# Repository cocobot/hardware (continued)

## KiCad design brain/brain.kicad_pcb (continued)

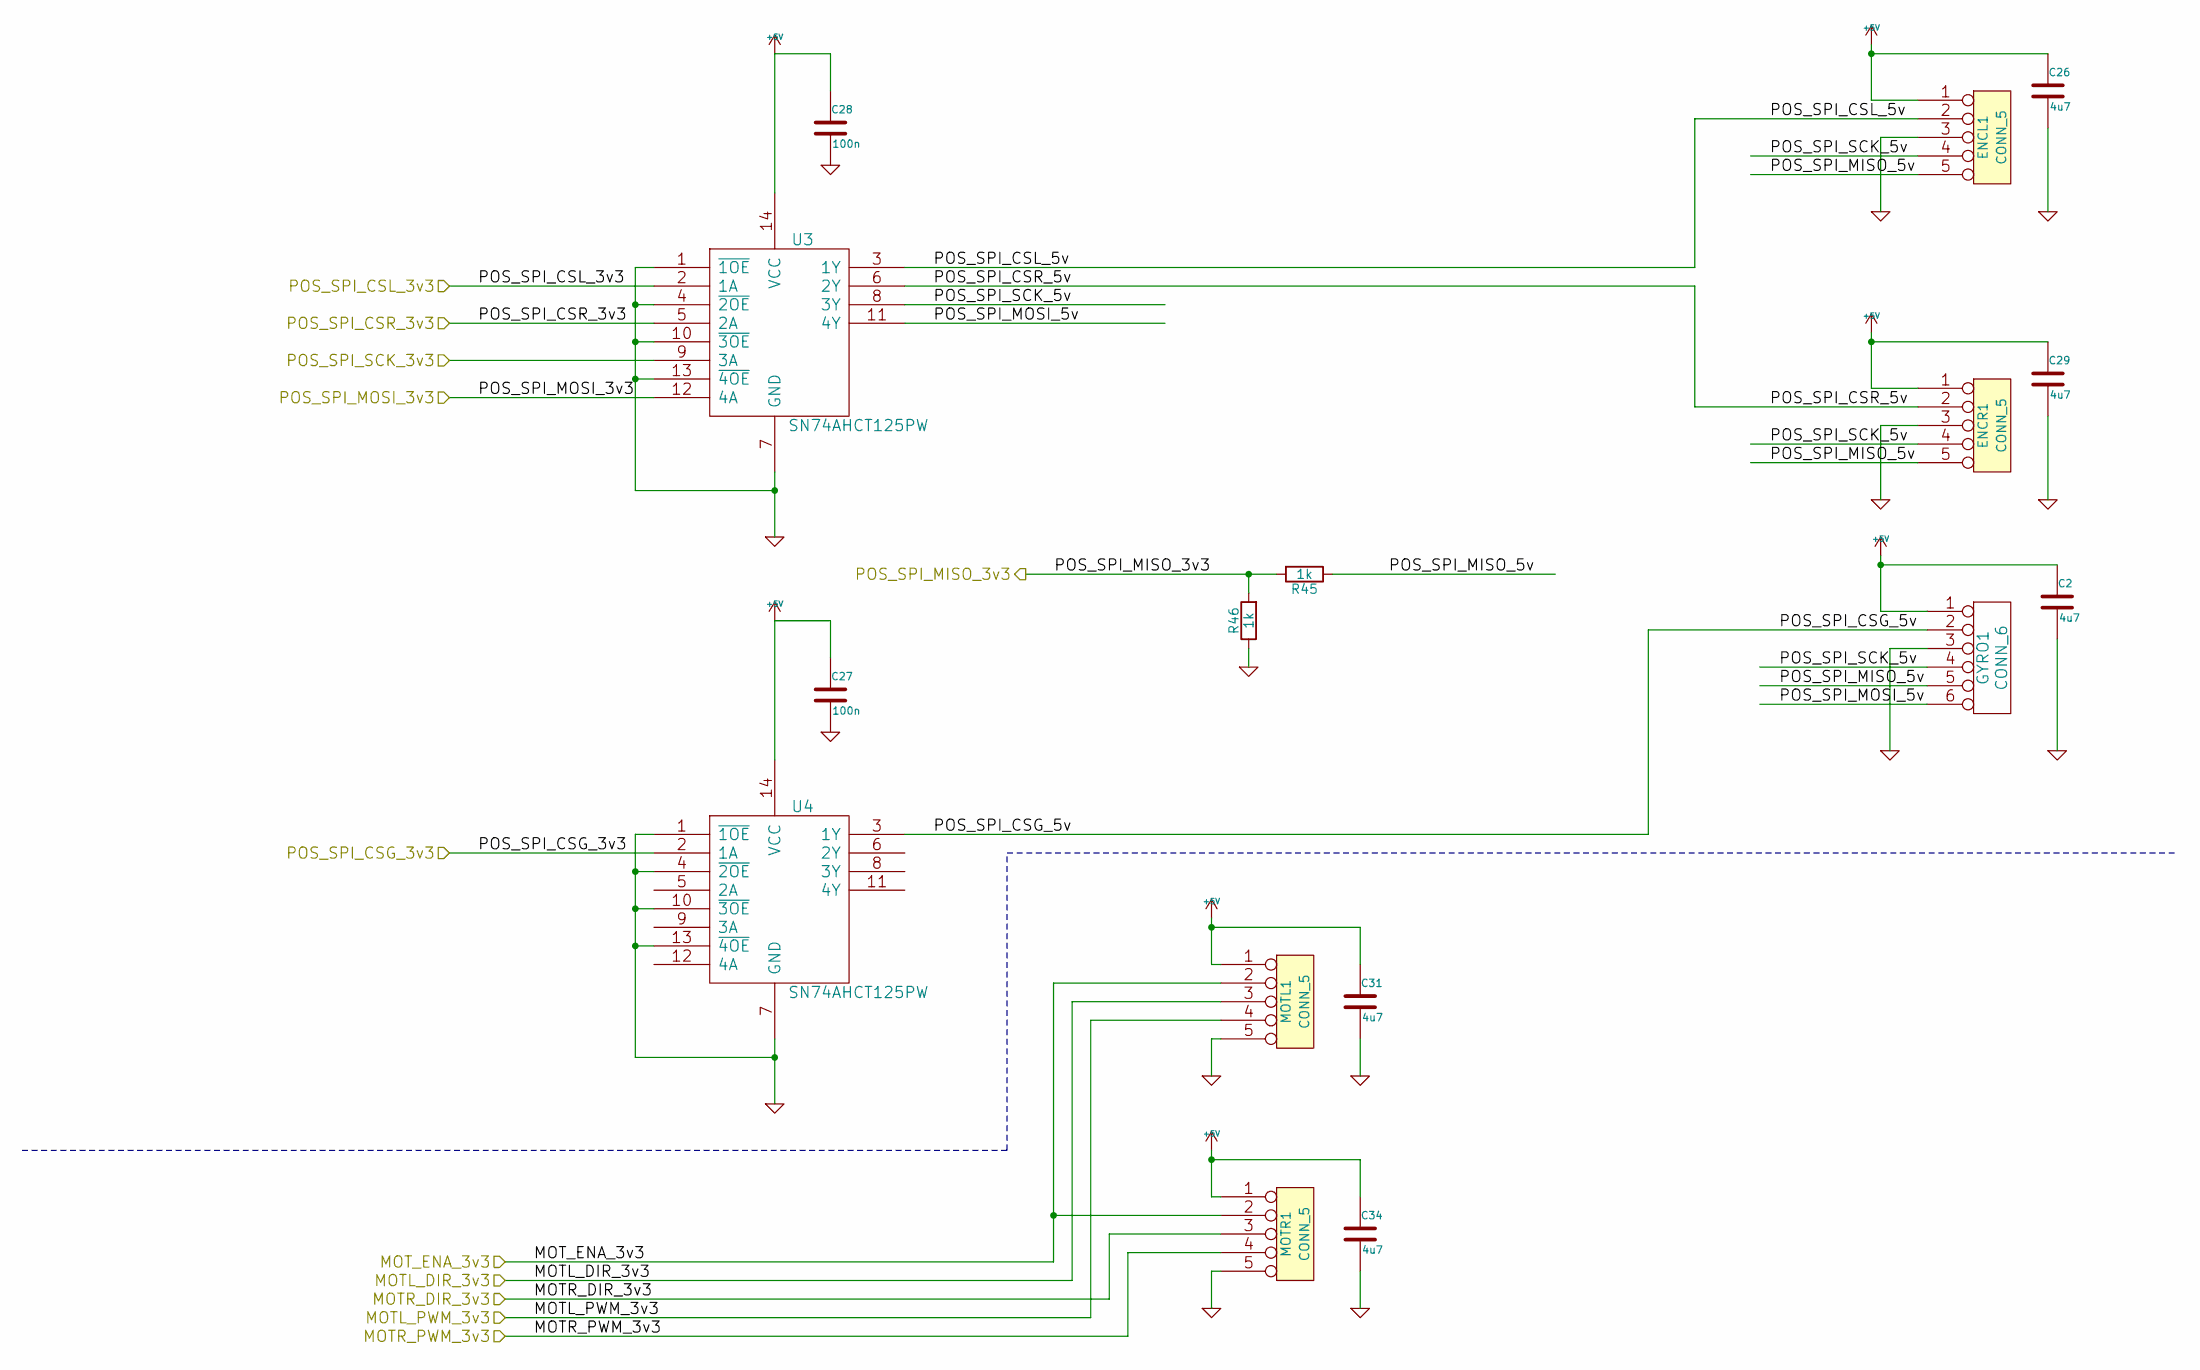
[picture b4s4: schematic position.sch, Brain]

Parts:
C2, C26, C29, C31, C34: 4u7; C_0603
C27, C28: 100n; C_0603
ENCL1: CONN_5; Socket_MOLEX-KK-RM2-54mm_Lock_5pin_straight
ENCR1: CONN_5; Socket_MOLEX-KK-RM2-54mm_Lock_5pin_straight
GYRO1: CONN_6; Socket_MOLEX-KK-RM2-54mm_Lock_6pin_straight
MOTL1: CONN_5; Socket_MOLEX-KK-RM2-54mm_Lock_5pin_straight
MOTR1: CONN_5; Socket_MOLEX-KK-RM2-54mm_Lock_5pin_straight
R45, R46: 1k; R_0603
U3, U4: SN74AHCT125PW; TSSOP-14_4.4x5mm_Pitch0.65mm

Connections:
+5V: C2.1, C26.1, C27.1, C28.1, C29.1, C31.1, C34.1, ENCL1.1, ENCR1.1, GYRO1.1, MOTL1.1, MOTR1.1, U3.14 (VCC), U4.14 (VCC); also elsewhere on the board
/DC motor/MOT_ENA_3v3: MOTL1.2, MOTR1.2; also elsewhere on the board
/Position/MOTL_DIR_3v3: MOTL1.3; also elsewhere on the board
/Position/MOTL_PWM_3v3: MOTL1.4; also elsewhere on the board
/Position/MOTR_DIR_3v3: MOTR1.3; also elsewhere on the board
/Position/MOTR_PWM_3v3: MOTR1.4; also elsewhere on the board
/Position/POS_SPI_CSG_3v3: U4.2 (1A); also elsewhere on the board
/Position/POS_SPI_CSG_5v: GYRO1.2, U4.3 (1Y)
/Position/POS_SPI_CSL_3v3: U3.2 (1A); also elsewhere on the board
/Position/POS_SPI_CSL_5v: ENCL1.2, U3.3 (1Y)
/Position/POS_SPI_CSR_3v3: U3.5 (2A); also elsewhere on the board
/Position/POS_SPI_CSR_5v: ENCR1.2, U3.6 (2Y)
/Position/POS_SPI_MISO_3v3: R45.2, R46.2; also elsewhere on the board
/Position/POS_SPI_MISO_5v: ENCL1.5, ENCR1.5, GYRO1.5, R45.1
/Position/POS_SPI_MOSI_3v3: U3.12 (4A); also elsewhere on the board
/Position/POS_SPI_MOSI_5v: GYRO1.6, U3.11 (4Y)
/Position/POS_SPI_SCK_3v3: U3.9 (3A); also elsewhere on the board
/Position/POS_SPI_SCK_5v: ENCL1.4, ENCR1.4, GYRO1.4, U3.8 (3Y)
GND: C2.2, C26.2, C27.2, C28.2, C29.2, C31.2, C34.2, ENCL1.3, ENCR1.3, GYRO1.3, MOTL1.5, MOTR1.5, R46.1, U3.1 (~1OE), U3.4 (~2OE), U3.7 (GND), U3.10 (~3OE), U3.13 (~4OE), U4.1 (~1OE), U4.4 (~2OE), U4.7 (GND), U4.10 (~3OE), U4.13 (~4OE); also elsewhere on the board

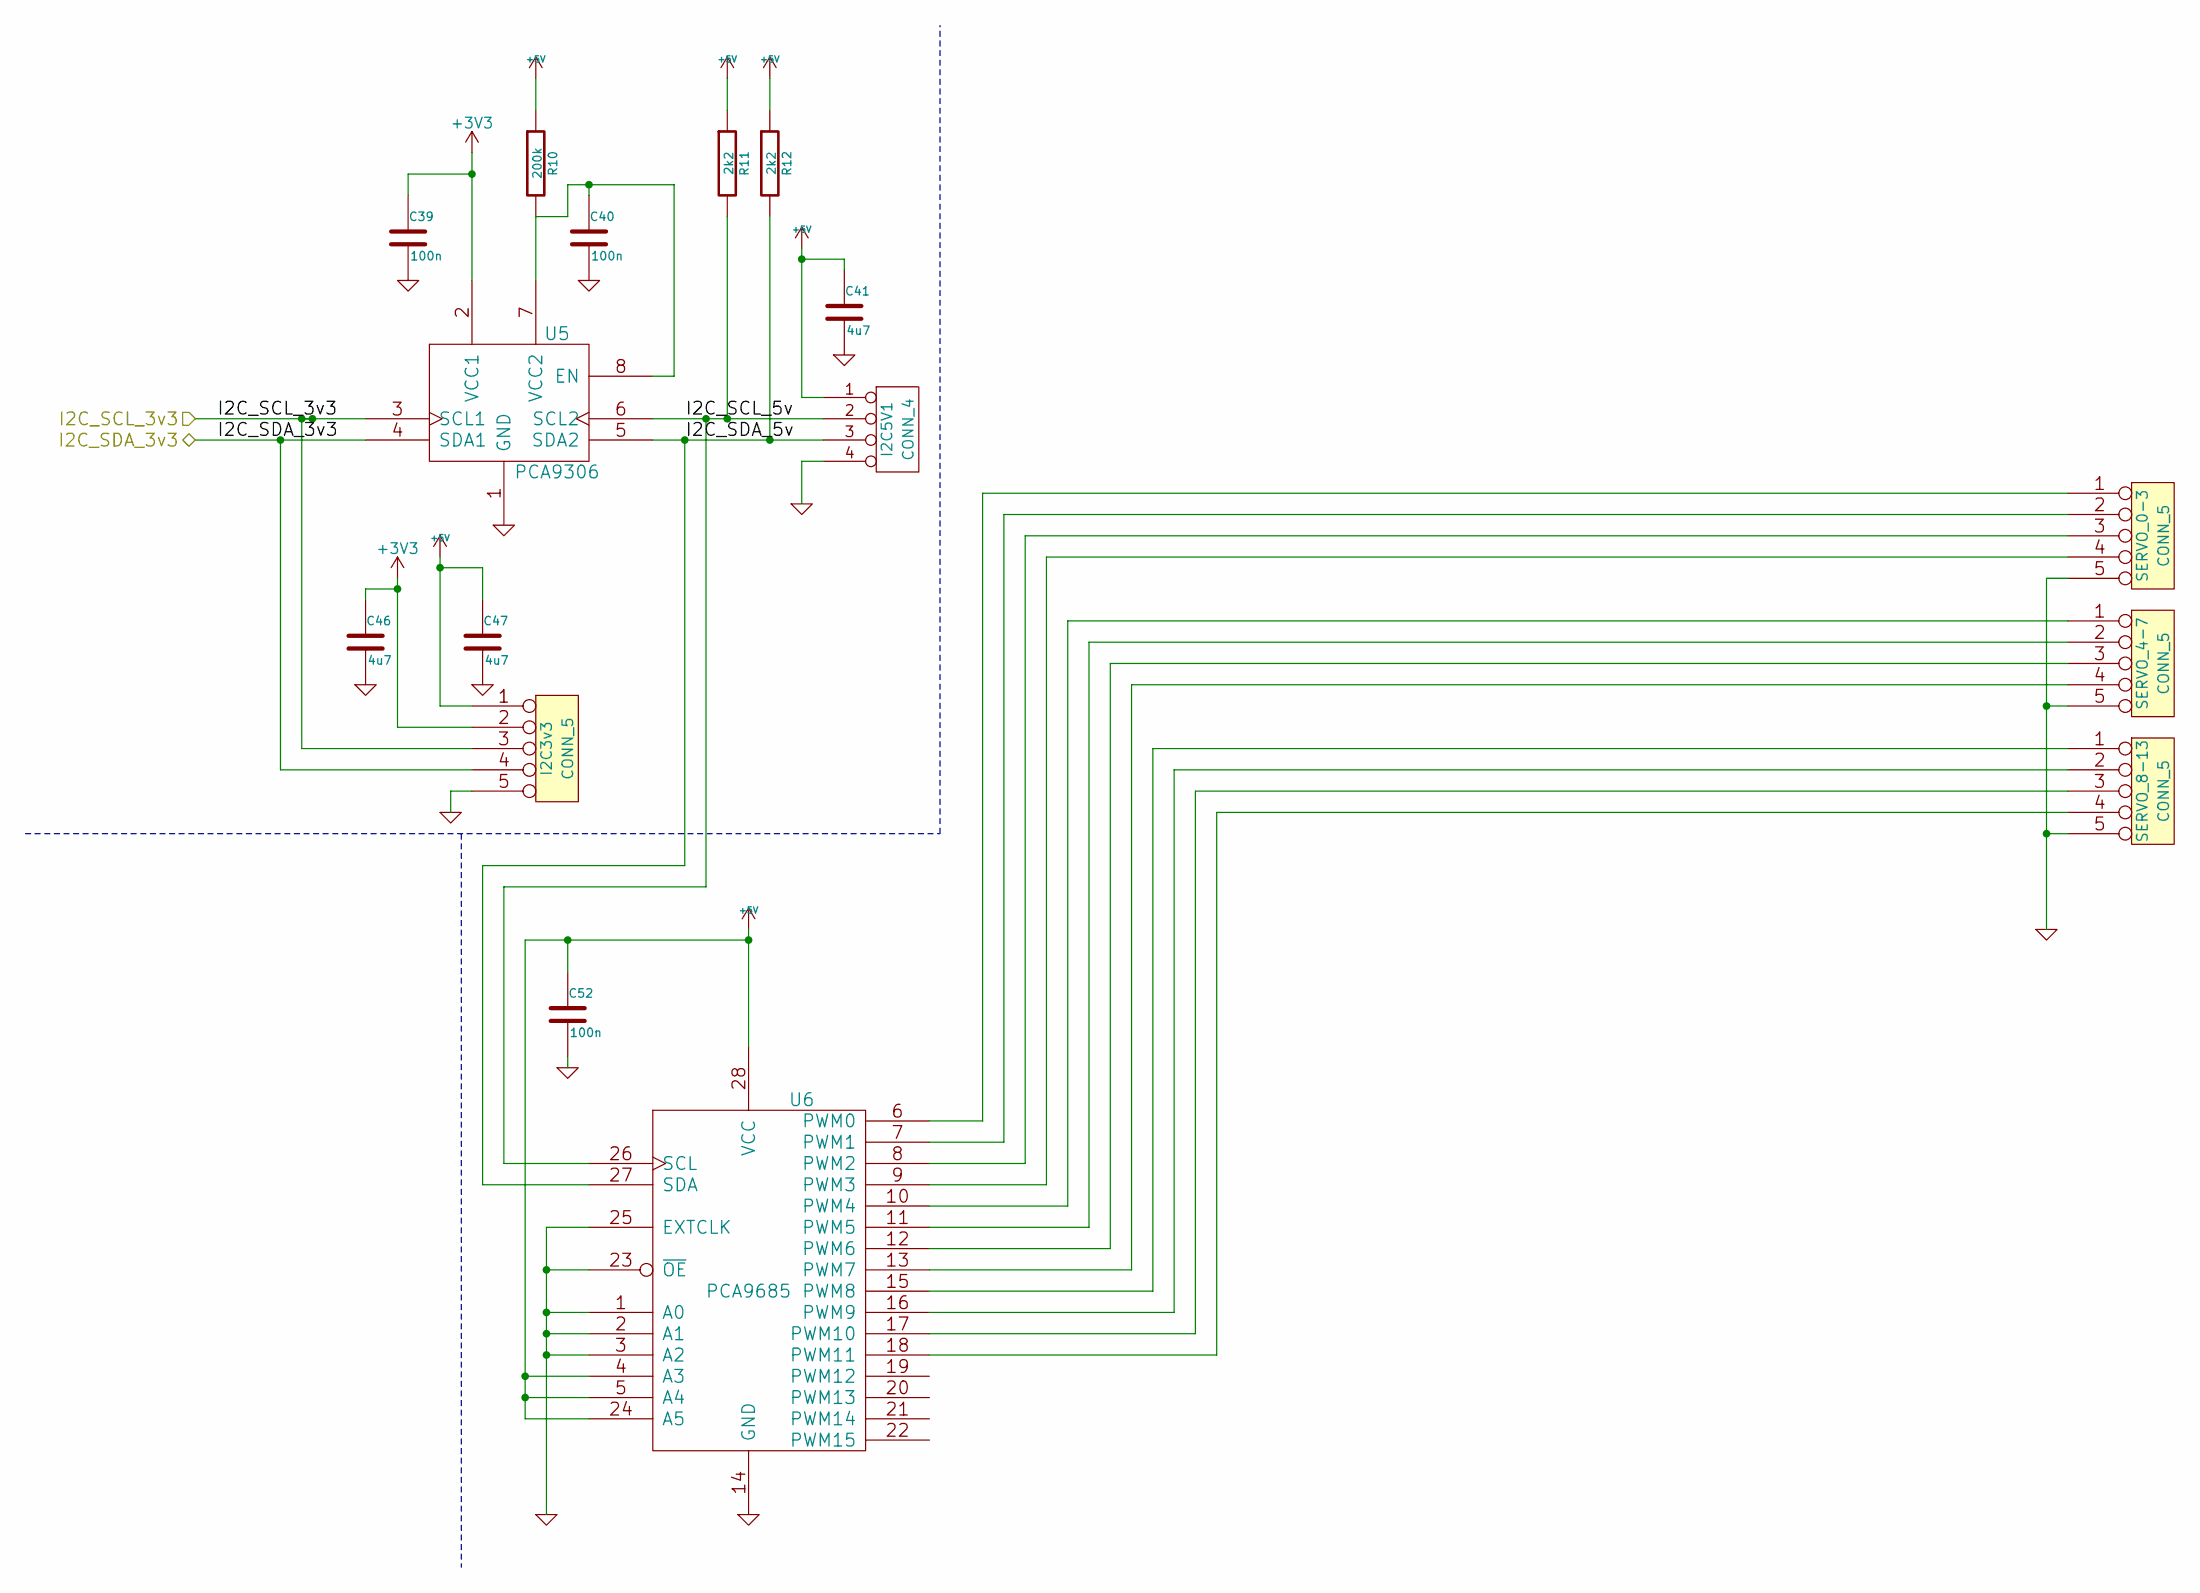
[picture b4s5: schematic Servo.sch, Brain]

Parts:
C39, C40, C52: 100n; C_0603
C41, C46, C47: 4u7; C_0603
I2C3v3: CONN_5; Socket_MOLEX-KK-RM2-54mm_Lock_5pin_straight
I2C5V1: CONN_4; Socket_MOLEX-KK-RM2-54mm_Lock_4pin_straight
R10: 200k; R_0603
R11, R12: 2k2; R_0603
SERVO_0-3, SERVO_4-7, SERVO_8-13: CONN_5; Socket_MOLEX-KK-RM2-54mm_Lock_5pin_straight
U5: PCA9306; SO-8
U6: PCA9685; TSSOP-28_4.4x9.7mm_Pitch0.65mm

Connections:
+3V3: C39.1, C46.1, I2C3v3.2, U5.2 (VCC1); also elsewhere on the board
+5V: C41.1, C47.1, C52.1, I2C3v3.1, I2C5V1.1, R10.1, R11.1, R12.1, U6.4 (A3), U6.5 (A4), U6.24 (A5), U6.28 (VCC); also elsewhere on the board
/Servo/I2C_SCL_3v3: I2C3v3.3, U5.3 (SCL1); also elsewhere on the board
/Servo/I2C_SCL_5v: I2C5V1.2, R11.2, U5.6 (SCL2), U6.26 (SCL)
/Servo/I2C_SDA_3v3: I2C3v3.4, U5.4 (SDA1); also elsewhere on the board
/Servo/I2C_SDA_5v: I2C5V1.3, R12.2, U5.5 (SDA2), U6.27 (SDA)
GND: C39.2, C40.2, C41.2, C46.2, C47.2, C52.2, I2C3v3.5, I2C5V1.4, SERVO_0-3.5, SERVO_4-7.5, SERVO_8-13.5, U5.1 (GND), U6.1 (A0), U6.2 (A1), U6.3 (A2), U6.14 (GND), U6.23 (~OE), U6.25 (EXTCLK); also elsewhere on the board
unnamed: C40.1, R10.2, U5.7 (VCC2), U5.8 (EN)
unnamed: SERVO_0-3.1, U6.6 (PWM0)
unnamed: SERVO_0-3.2, U6.7 (PWM1)
unnamed: SERVO_0-3.3, U6.8 (PWM2)
unnamed: SERVO_0-3.4, U6.9 (PWM3)
unnamed: SERVO_4-7.1, U6.10 (PWM4)
unnamed: SERVO_4-7.2, U6.11 (PWM5)
unnamed: SERVO_4-7.3, U6.12 (PWM6)
unnamed: SERVO_4-7.4, U6.13 (PWM7)
unnamed: SERVO_8-13.1, U6.15 (PWM8)
unnamed: SERVO_8-13.2, U6.16 (PWM9)
unnamed: SERVO_8-13.3, U6.17 (PWM10)
unnamed: SERVO_8-13.4, U6.18 (PWM11)

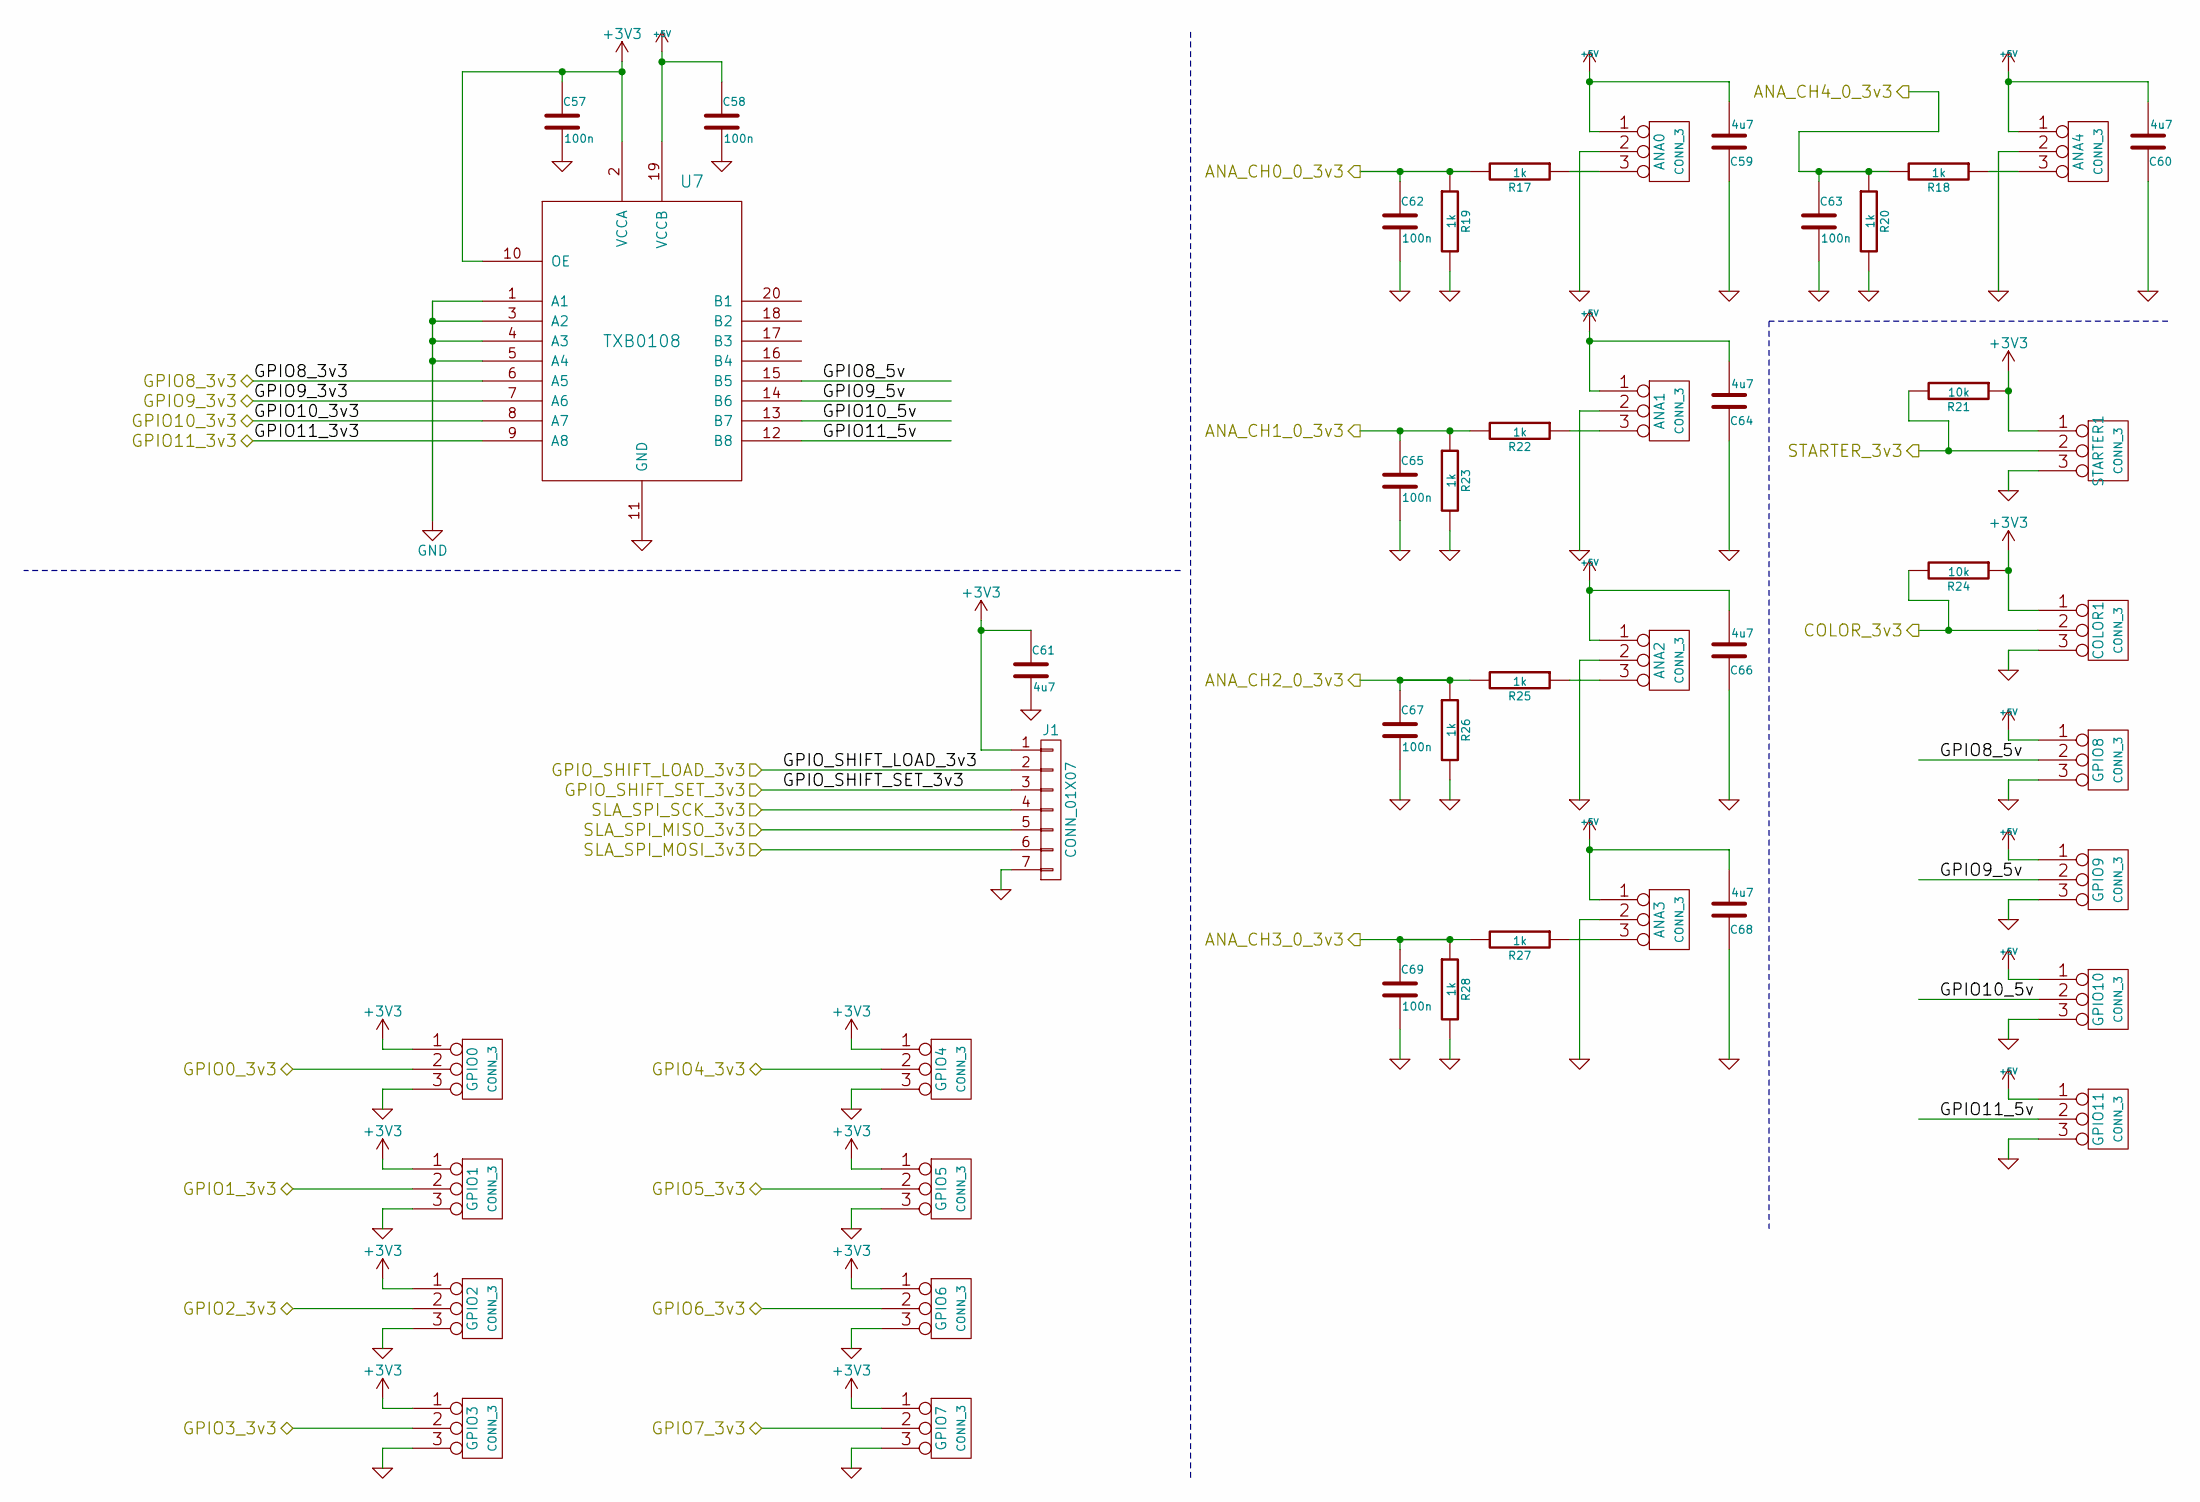
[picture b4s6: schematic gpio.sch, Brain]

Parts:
ANA0, ANA1, ANA2, ANA3, ANA4: CONN_3; Socket_MOLEX-KK-RM2-54mm_Lock_3pin_straight
C57, C58, C62, C63, C65, C67, C69: 100n; C_0603
C59, C60, C61, C64, C66, C68: 4u7; C_0603
COLOR1: CONN_3; Socket_MOLEX-KK-RM2-54mm_Lock_3pin_straight
GPIO0, GPIO1, GPIO2, GPIO3, GPIO4, GPIO5, GPIO6, GPIO7, GPIO8, GPIO9, GPIO10, GPIO11: CONN_3; Socket_MOLEX-KK-RM2-54mm_Lock_3pin_straight
J1: CONN_01X07; Socket_MOLEX-KK-RM2-54mm_Lock_7pin_straight
R17, R18, R19, R20, R22, R23, R25, R26, R27, R28: 1k; R_0603
R21, R24: 10k; R_0603
STARTER1: CONN_3; Socket_MOLEX-KK-RM2-54mm_Lock_3pin_straight
U7: TXB0108; TSSOP-20_4.4x6.5mm_Pitch0.65mm

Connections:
+3V3: C57.1, C61.1, COLOR1.1, GPIO0.1, GPIO1.1, GPIO2.1, GPIO3.1, GPIO4.1, GPIO5.1, GPIO6.1, GPIO7.1, J1.1, R21.1, R24.1, STARTER1.1, U7.2 (VCCA), U7.10 (OE); also elsewhere on the board
+5V: ANA0.1, ANA1.1, ANA2.1, ANA3.1, ANA4.1, C58.1, C59.2, C60.2, C64.2, C66.2, C68.2, GPIO8.1, GPIO9.1, GPIO10.1, GPIO11.1, U7.19 (VCCB); also elsewhere on the board
/GPIO/ANA_CH0_0_3v3: C62.1, R17.2, R19.1; also elsewhere on the board
/GPIO/ANA_CH1_0_3v3: C65.1, R22.2, R23.1; also elsewhere on the board
/GPIO/ANA_CH2_0_3v3: C67.1, R25.2, R26.1; also elsewhere on the board
/GPIO/ANA_CH3_0_3v3: C69.1, R27.2, R28.1; also elsewhere on the board
/GPIO/ANA_CH4_0_3v3: C63.1, R18.2, R20.1; also elsewhere on the board
/GPIO/COLOR_3v3: COLOR1.2 (PM), R24.2; also elsewhere on the board
/GPIO/GPIO0_3v3: GPIO0.2 (PM); also elsewhere on the board
/GPIO/GPIO1_3v3: GPIO1.2 (PM); also elsewhere on the board
/GPIO/GPIO2_3v3: GPIO2.2 (PM); also elsewhere on the board
/GPIO/GPIO3_3v3: GPIO3.2 (PM); also elsewhere on the board
/GPIO/GPIO4_3v3: GPIO4.2 (PM); also elsewhere on the board
/GPIO/GPIO5_3v3: GPIO5.2 (PM); also elsewhere on the board
/GPIO/GPIO6_3v3: GPIO6.2 (PM); also elsewhere on the board
/GPIO/GPIO7_3v3: GPIO7.2 (PM); also elsewhere on the board
/GPIO/GPIO8_3v3: U7.6 (A5); also elsewhere on the board
/GPIO/GPIO8_5v: GPIO8.2 (PM), U7.15 (B5)
/GPIO/GPIO9_3v3: U7.7 (A6); also elsewhere on the board
/GPIO/GPIO9_5v: GPIO9.2 (PM), U7.14 (B6)
/GPIO/GPIO10_3v3: U7.8 (A7); also elsewhere on the board
/GPIO/GPIO10_5v: GPIO10.2 (PM), U7.13 (B7)
/GPIO/GPIO11_3v3: U7.9 (A8); also elsewhere on the board
/GPIO/GPIO11_5v: GPIO11.2 (PM), U7.12 (B8)
/GPIO/GPIO_SHIFT_LOAD_3v3: J1.2; also elsewhere on the board
/GPIO/GPIO_SHIFT_SET_3v3: J1.3; also elsewhere on the board
/GPIO/SLA_SPI_MISO_3v3: J1.5; also elsewhere on the board
/GPIO/SLA_SPI_MOSI_3v3: J1.6; also elsewhere on the board
/GPIO/SLA_SPI_SCK_3v3: J1.4; also elsewhere on the board
/GPIO/STARTER_3v3: R21.2, STARTER1.2 (PM); also elsewhere on the board
GND: ANA0.2 (PM), ANA1.2 (PM), ANA2.2 (PM), ANA3.2 (PM), ANA4.2 (PM), C57.2, C58.2, C59.1, C60.1, C61.2, C62.2, C63.2, C64.1, C65.2, C66.1, C67.2, C68.1, C69.2, COLOR1.3, GPIO0.3, GPIO1.3, GPIO2.3, GPIO3.3, GPIO4.3, GPIO5.3, GPIO6.3, GPIO7.3, GPIO8.3, GPIO9.3, GPIO10.3, GPIO11.3, J1.7, R19.2, R20.2, R23.2, R26.2, R28.2, STARTER1.3, U7.1 (A1), U7.3 (A2), U7.4 (A3), U7.5 (A4), U7.11 (GND); also elsewhere on the board
unnamed: ANA0.3, R17.1
unnamed: ANA1.3, R22.1
unnamed: ANA2.3, R25.1
unnamed: ANA3.3, R27.1
unnamed: ANA4.3, R18.1

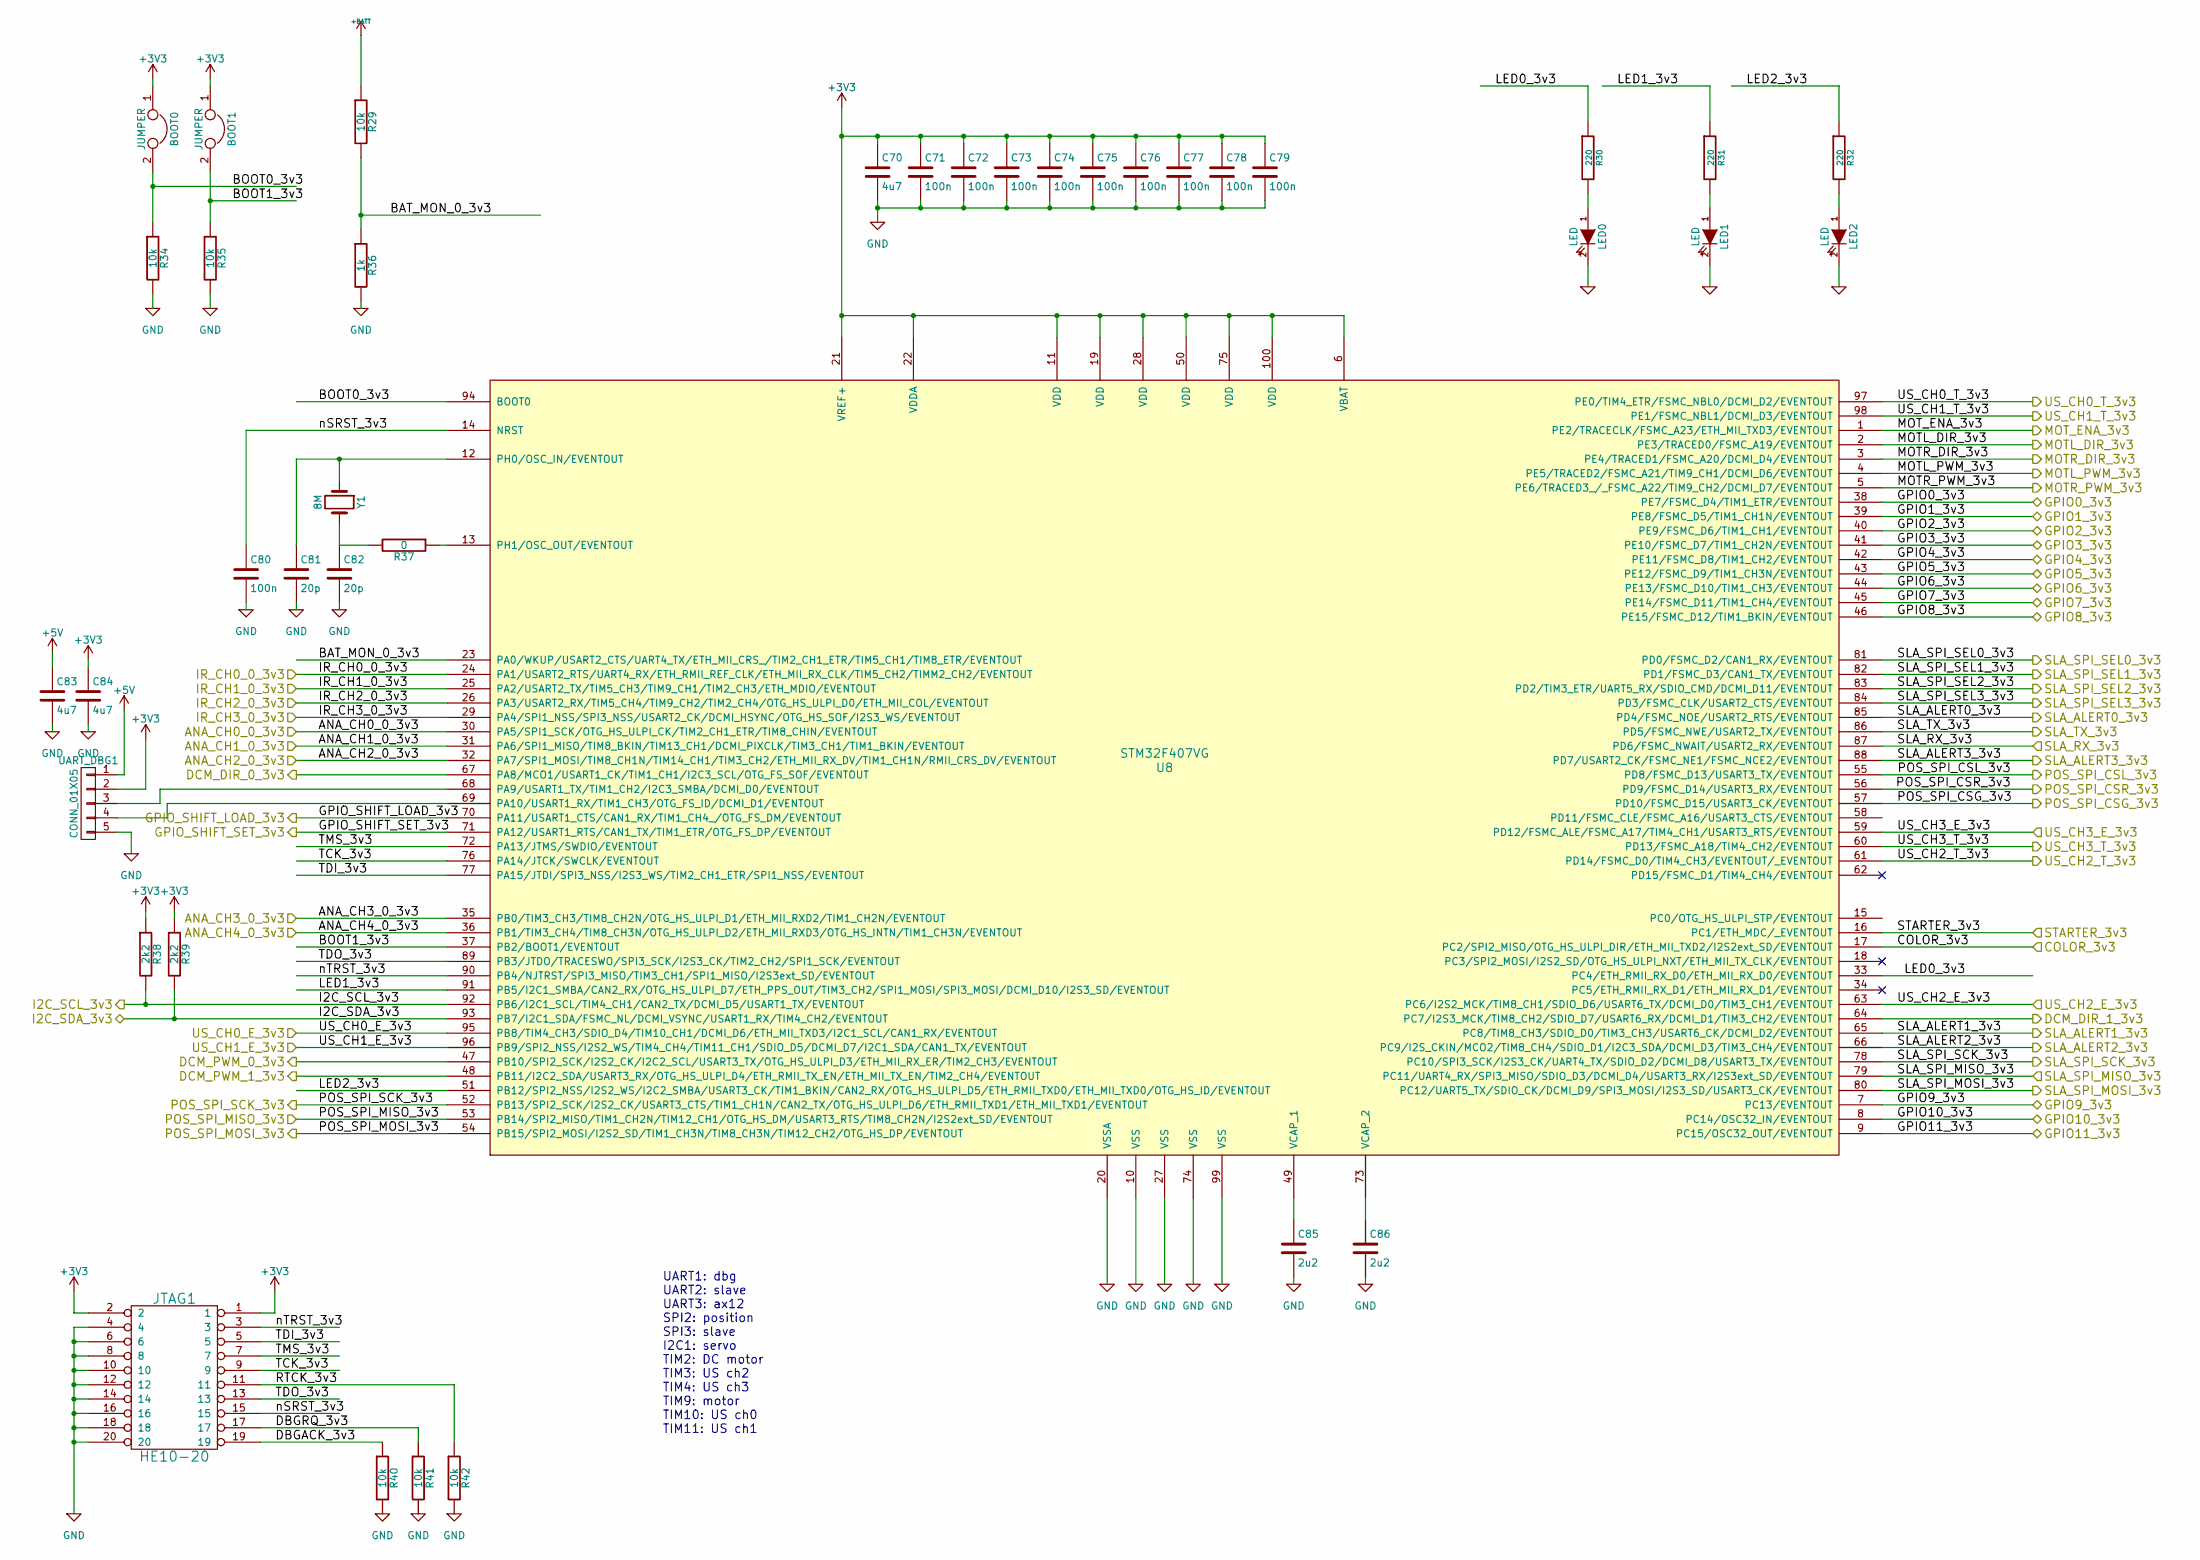
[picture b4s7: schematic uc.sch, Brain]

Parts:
BOOT0, BOOT1: JUMPER; Pin_Header_Straight_1x02_Pitch2.54mm
C70, C83, C84: 4u7; C_0603
C71, C72, C73, C74, C75, C76, C77, C78, C79, C80: 100n; C_0603
C81, C82: 20p; C_0603
C85, C86: 2u2; C_0603
JTAG1: HE10-20; HE10_20D
LED0, LED1, LED2: LED; LED-0603
R29, R34, R35, R40, R41, R42: 10k; R_0603
R30, R31, R32: 220; R_0603
R36: 1k; R_0603
R37: 0; R_0603
R38, R39: 2k2; R_0603
U8: STM32F407VG; LQFP-100_14x14mm_Pitch0.5mm
UART_DBG1: CONN_01X05; Socket_MOLEX-KK-RM2-54mm_Lock_5pin_straight
Y1: 8M; Crystal_HC49-SD_SMD

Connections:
+3V3: BOOT0.1, BOOT1.1, C70.1, C71.1, C72.1, C73.1, C74.1, C75.1, C76.1, C77.1, C78.1, C79.1, C84.1, JTAG1.1, JTAG1.2, R38.1, R39.1, U8.6 (VBAT), U8.11 (VDD), U8.19 (VDD), U8.21 (VREF+), U8.22 (VDDA), U8.28 (VDD), U8.50 (VDD), U8.75 (VDD), U8.100 (VDD), UART_DBG1.2; also elsewhere on the board
+5V: C83.1, UART_DBG1.1; also elsewhere on the board
+BATT: R29.1; also elsewhere on the board
/DC motor/DCM0_DIR_3v3: U8.67 (PA8/MCO1/USART1_CK/TIM1_CH1/I2C3_SCL/OT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); also elsewhere on the board
/DC motor/DCM0_PWM_3v3: U8.47 (PB10/SPI2_SCK/I2S2_CK/I2C2_SCL/USART3_T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); also elsewhere on the board
/DC motor/DCM1_DIR_3v3: U8.64 (PC7/I2S3_MCK/TIM8_CH2/SDIO_D7/USART6_RX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)
/DC motor/DCM1_PWM_3v3: U8.48 (PB11/I2C2_SDA/USART3_RX/OTG_HS_ULPI_D4/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)
/DC motor/MOT_ENA_3v3: U8.1 (PE2/TRACECLK/FSMC_A23/ETH_MII_TXD3/EVEN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); also elsewhere on the board
/GPIO/ANA_CH0_0_3v3: U8.30 (PA5/SPI1_SCK/OTG_HS_ULPI_CK/TIM2_CH1_ET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); also elsewhere on the board
/GPIO/ANA_CH1_0_3v3: U8.31 (PA6/SPI1_MISO/TIM8_BKIN/TIM13_CH1/DCMI_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); also elsewhere on the board
/GPIO/ANA_CH2_0_3v3: U8.32 (PA7/SPI1_MOSI/TIM8_CH1N/TIM14_CH1/TIM3_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); also elsewhere on the board
/GPIO/ANA_CH3_0_3v3: U8.35 (PB0/TIM3_CH3/TIM8_CH2N/OTG_HS_ULPI_D1/E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); also elsewhere on the board
/GPIO/ANA_CH4_0_3v3: U8.36 (PB1/TIM3_CH4/TIM8_CH3N/OTG_HS_ULPI_D2/E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); also elsewhere on the board
/GPIO/COLOR_3v3: U8.17 (PC2/SPI2_MISO/OTG_HS_ULPI_DIR/ETH_MII_T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); also elsewhere on the board
/GPIO/GPIO0_3v3: U8.38 (PE7/FSMC_D4/TIM1_ETR/EVENTOUT); also elsewhere on the board
/GPIO/GPIO1_3v3: U8.39 (PE8/FSMC_D5/TIM1_CH1N/EVENTOUT); also elsewhere on the board
/GPIO/GPIO2_3v3: U8.40 (PE9/FSMC_D6/TIM1_CH1/EVENTOUT); also elsewhere on the board
/GPIO/GPIO3_3v3: U8.41 (PE10/FSMC_D7/TIM1_CH2N/EVENTOUT); also elsewhere on the board
/GPIO/GPIO4_3v3: U8.42 (PE11/FSMC_D8/TIM1_CH2/EVENTOUT); also elsewhere on the board
/GPIO/GPIO5_3v3: U8.43 (PE12/FSMC_D9/TIM1_CH3N/EVENTOUT); also elsewhere on the board
/GPIO/GPIO6_3v3: U8.44 (PE13/FSMC_D10/TIM1_CH3/EVENTOUT); also elsewhere on the board
/GPIO/GPIO7_3v3: U8.45 (PE14/FSMC_D11/TIM1_CH4/EVENTOUT); also elsewhere on the board
/GPIO/GPIO8_3v3: U8.46 (PE15/FSMC_D12/TIM1_BKIN/EVENTOUT); also elsewhere on the board
/GPIO/GPIO9_3v3: U8.7 (PC13/EVENTOUT); also elsewhere on the board
/GPIO/GPIO10_3v3: U8.8 (PC14/OSC32_IN/EVENTOUT); also elsewhere on the board
/GPIO/GPIO11_3v3: U8.9 (PC15/OSC32_OUT/EVENTOUT); also elsewhere on the board
/GPIO/GPIO_SHIFT_LOAD_3v3: U8.70 (PA11/USART1_CTS/CAN1_RX/TIM1_CH4_/OTG_F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); also elsewhere on the board
/GPIO/GPIO_SHIFT_SET_3v3: U8.71 (PA12/USART1_RTS/CAN1_TX/TIM1_ETR/OTG_FS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); also elsewhere on the board
/GPIO/SLA_SPI_MISO_3v3: U8.79 (PC11/UART4_RX/SPI3_MISO/SDIO_D3/DCMI_D4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); also elsewhere on the board
/GPIO/SLA_SPI_MOSI_3v3: U8.80 (PC12/UART5_TX/SDIO_CK/DCMI_D9/SPI3_MOSI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); also elsewhere on the board
/GPIO/SLA_SPI_SCK_3v3: U8.78 (PC10/SPI3_SCK/I2S3_CK/UART4_TX/SDIO_D2/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); also elsewhere on the board
/GPIO/STARTER_3v3: U8.16 (PC1/ETH_MDC/_EVENTOUT); also elsewhere on the board
/Position/MOTL_DIR_3v3: U8.2 (PE3/TRACED0/FSMC_A19/EVENTOUT); also elsewhere on the board
/Position/MOTL_PWM_3v3: U8.4 (PE5/TRACED2/FSMC_A21/TIM9_CH1/DCMI_D6/E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); also elsewhere on the board
/Position/MOTR_DIR_3v3: U8.3 (PE4/TRACED1/FSMC_A20/DCMI_D4/EVENTOUT); also elsewhere on the board
/Position/MOTR_PWM_3v3: U8.5 (PE6/TRACED3_/_FSMC_A22/TIM9_CH2/DCMI_D7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); also elsewhere on the board
/Position/POS_SPI_CSG_3v3: U8.57 (PD10/FSMC_D15/USART3_CK/EVENTOUT); also elsewhere on the board
/Position/POS_SPI_CSL_3v3: U8.55 (PD8/FSMC_D13/USART3_TX/EVENTOUT); also elsewhere on the board
/Position/POS_SPI_CSR_3v3: U8.56 (PD9/FSMC_D14/USART3_RX/EVENTOUT); also elsewhere on the board
/Position/POS_SPI_MISO_3v3: U8.53 (PB14/SPI2_MISO/TIM1_CH2N/TIM12_CH1/OTG_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); also elsewhere on the board
/Position/POS_SPI_MOSI_3v3: U8.54 (PB15/SPI2_MOSI/I2S2_SD/TIM1_CH3N/TIM8_C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); also elsewhere on the board
/Position/POS_SPI_SCK_3v3: U8.52 (PB13/SPI2_SCK/I2S2_CK/USART3_CTS/TIM1_C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); also elsewhere on the board
/Servo/I2C_SCL_3v3: R38.2, U8.92 (PB6/I2C1_SCL/TIM4_CH1/CAN2_TX/DCMI_D5/U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); also elsewhere on the board
/Servo/I2C_SDA_3v3: R39.2, U8.93 (PB7/I2C1_SDA/FSMC_NL/DCMI_VSYNC/USART1_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); also elsewhere on the board
/Slave/SLA_ALERT0_3v3: U8.85 (PD4/FSMC_NOE/USART2_RTS/EVENTOUT); also elsewhere on the board
/Slave/SLA_ALERT1_3v3: U8.65 (PC8/TIM8_CH3/SDIO_D0/TIM3_CH3/USART6_CK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); also elsewhere on the board
/Slave/SLA_ALERT2_3v3: U8.66 (PC9/I2S_CKIN/MCO2/TIM8_CH4/SDIO_D1/I2C3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); also elsewhere on the board
/Slave/SLA_ALERT3_3v3: U8.88 (PD7/USART2_CK/FSMC_NE1/FSMC_NCE2/EVENTO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); also elsewhere on the board
/Slave/SLA_RX_3v3: U8.87 (PD6/FSMC_NWAIT/USART2_RX/EVENTOUT); also elsewhere on the board
/Slave/SLA_SPI_SEL0_3v3: U8.81 (PD0/FSMC_D2/CAN1_RX/EVENTOUT); also elsewhere on the board
/Slave/SLA_SPI_SEL1_3v3: U8.82 (PD1/FSMC_D3/CAN1_TX/EVENTOUT); also elsewhere on the board
/Slave/SLA_SPI_SEL2_3v3: U8.83 (PD2/TIM3_ETR/UART5_RX/SDIO_CMD/DCMI_D11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); also elsewhere on the board
/Slave/SLA_SPI_SEL3_3v3: U8.84 (PD3/FSMC_CLK/USART2_CTS/EVENTOUT); also elsewhere on the board
/Slave/SLA_TX_3v3: U8.86 (PD5/FSMC_NWE/USART2_TX/EVENTOUT); also elsewhere on the board
/USIR/IR_CH0_0_3v3: U8.24 (PA1/USART2_RTS/UART4_RX/ETH_RMII_REF_CL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); also elsewhere on the board
/USIR/IR_CH1_0_3v3: U8.25 (PA2/USART2_TX/TIM5_CH3/TIM9_CH1/TIM2_CH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); also elsewhere on the board
/USIR/IR_CH2_0_3v3: U8.26 (PA3/USART2_RX/TIM5_CH4/TIM9_CH2/TIM2_CH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); also elsewhere on the board
/USIR/IR_CH3_0_3v3: U8.29 (PA4/SPI1_NSS/SPI3_NSS/USART2_CK/DCMI_HS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); also elsewhere on the board
/USIR/US_CH0_E_3v3: U8.95 (PB8/TIM4_CH3/SDIO_D4/TIM10_CH1/DCMI_D6/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); also elsewhere on the board
/USIR/US_CH0_T_3v3: U8.97 (PE0/TIM4_ETR/FSMC_NBL0/DCMI_D2/EVENTOUT); also elsewhere on the board
/USIR/US_CH1_E_3v3: U8.96 (PB9/SPI2_NSS/I2S2_WS/TIM4_CH4/TIM11_CH1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); also elsewhere on the board
/USIR/US_CH1_T_3v3: U8.98 (PE1/FSMC_NBL1/DCMI_D3/EVENTOUT); also elsewhere on the board
/USIR/US_CH2_E_3v3: U8.63 (PC6/I2S2_MCK/TIM8_CH1/SDIO_D6/USART6_TX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); also elsewhere on the board
/USIR/US_CH2_T_3v3: U8.61 (PD14/FSMC_D0/TIM4_CH3/EVENTOUT/_EVENTOUT); also elsewhere on the board
/USIR/US_CH3_E_3v3: U8.59 (PD12/FSMC_ALE/FSMC_A17/TIM4_CH1/USART3_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); also elsewhere on the board
/USIR/US_CH3_T_3v3: U8.60 (PD13/FSMC_A18/TIM4_CH2/EVENTOUT); also elsewhere on the board
/uc/BAT_MON_0_3v3: R29.2, R36.1, U8.23 (PA0/WKUP/USART2_CTS/UART4_TX/ETH_MII_CR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)
/uc/BOOT0_3v3: BOOT0.2, R34.1, U8.94 (BOOT0)
/uc/BOOT1_3v3: BOOT1.2, R35.1, U8.37 (PB2/BOOT1/EVENTOUT)
/uc/DBGACK_3v3: JTAG1.19, R40.1
/uc/DBGRQ_3v3: JTAG1.17, R41.1
/uc/LED0_3v3: R30.1, U8.33 (PC4/ETH_RMII_RX_D0/ETH_MII_RX_D0/EVENTO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)
/uc/LED1_3v3: R31.1, U8.91 (PB5/I2C1_SMBA/CAN2_RX/OTG_HS_ULPI_D7/ET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)
/uc/LED2_3v3: R32.1, U8.51 (PB12/SPI2_NSS/I2S2_WS/I2C2_SMBA/USART3_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)
/uc/RTCK_3v3: JTAG1.11, R42.1
/uc/TCK_3v3: JTAG1.9, U8.76 (PA14/JTCK/SWCLK/EVENTOUT)
/uc/TDI_3v3: JTAG1.5, U8.77 (PA15/JTDI/SPI3_NSS/I2S3_WS/TIM2_CH1_ETR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)
/uc/TDO_3v3: JTAG1.13, U8.89 (PB3/JTDO/TRACESWO/SPI3_SCK/I2S3_CK/TIM2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)
/uc/TMS_3v3: JTAG1.7, U8.72 (PA13/JTMS/SWDIO/EVENTOUT)
/uc/nSRST_3v3: C80.1, JTAG1.15, U8.14 (NRST)
/uc/nTRST_3v3: JTAG1.3, U8.90 (PB4/NJTRST/SPI3_MISO/TIM3_CH1/SPI1_MISO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)
GND: C70.2, C71.2, C72.2, C73.2, C74.2, C75.2, C76.2, C77.2, C78.2, C79.2, C80.2, C81.2, C82.2, C83.2, C84.2, C85.2, C86.2, JTAG1.4, JTAG1.6, JTAG1.8, JTAG1.10, JTAG1.12, JTAG1.14, JTAG1.16, JTAG1.18, JTAG1.20, LED0.2 (K), LED1.2 (K), LED2.2 (K), R34.2, R35.2, R36.2, R40.2, R41.2, R42.2, U8.10 (VSS), U8.20 (VSSA), U8.27 (VSS), U8.74 (VSS), U8.99 (VSS), UART_DBG1.5; also elsewhere on the board
unnamed: C81.1, U8.12 (PH0/OSC_IN/EVENTOUT), Y1.1
unnamed: C82.1, R37.2, Y1.2
unnamed: C85.1, U8.49 (VCAP_1)
unnamed: C86.1, U8.73 (VCAP_2)
unnamed: LED0.1 (A), R30.2
unnamed: LED1.1 (A), R31.2
unnamed: LED2.1 (A), R32.2
unnamed: R37.1, U8.13 (PH1/OSC_OUT/EVENTOUT)
unnamed: U8.68 (PA9/USART1_TX/TIM1_CH2/I2C3_SMBA/DCMI_D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), UART_DBG1.3
unnamed: U8.69 (PA10/USART1_RX/TIM1_CH3/OTG_FS_ID/DCMI_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), UART_DBG1.4

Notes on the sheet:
UART1: dbg UART2: slave UART3: ax12 SPI2: position SPI3: slave I2C1: servo TIM2: DC motor TIM3: US ch2 TIM4: US ch3 TIM9: motor TIM10: US ch0 TIM11: US ch1
